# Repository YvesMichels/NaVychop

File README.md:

# navychop

**Autonomous flight experimentation platform — RC aircraft / embedded navigation / AI-assisted development**

`navychop` est un projet **scientifique, technique et ludique** consacré à l'expérimentation autour des pilotes autonomes pour aéronefs.

L'objectif est de construire, avec des moyens essentiellement amateurs, une chaîne complète de navigation et de pilotage autonome : **capteurs → estimation d'état → contrôle → actionneurs → télémétrie**, tout en explorant les limites de ce qui peut être réalisé avec une architecture embarquée légère.

Le projet sert également d'expérimentation sur une autre question :

> **Jusqu'où un projet technique développé par une seule personne, assistée par des IA génératives, peut-il aller face aux méthodes et moyens traditionnellement disponibles dans l'industrie ?**

Il ne s'agit pas de reproduire une architecture avionique industrielle certifiée, mais de mesurer concrètement les capacités, les limites, les compromis et les difficultés rencontrées lorsqu'une approche individuelle s'appuie fortement sur les outils modernes d'IA.

---

## Objectifs

Le projet poursuit plusieurs objectifs complémentaires :

* expérimenter les techniques de **navigation inertielle et de pilotage automatique** ;
* développer une centrale de navigation embarquée autour d'un microcontrôleur ;
* exploiter et fusionner plusieurs capteurs : IMU, baromètre, magnétomètre, GPS et éventuellement vision ;
* développer des lois de commande adaptées à un aéronef léger ;
* expérimenter différentes architectures d'estimation et de contrôle ;
* étudier les contraintes de calcul, de mémoire, de latence et de robustesse d'un système embarqué ;
* développer une chaîne complète allant du matériel embarqué au poste sol ;
* réaliser des essais en conditions réelles sur un aéronef radiocommandé ;
* utiliser les IA génératives comme **assistant de développement et de recherche**, et mesurer concrètement leur apport.

Une attention particulière est portée à la distinction entre :

1. ce qui est **théoriquement possible** ;
2. ce qui est **réalisable avec le matériel disponible** ;
3. ce qui fonctionne réellement **en simulation ou sur banc** ;
4. ce qui fonctionne **en vol**.

---

## Philosophie du projet

`navychop` est volontairement développé comme un projet personnel à vocation expérimentale.

Le but n'est pas de produire immédiatement un système industriel, certifiable ou commercialisable. Le but est au contraire de pouvoir tester rapidement des idées, constater leurs limites et conserver les résultats des expériences.

Le projet cherche notamment à répondre expérimentalement à des questions telles que :

* Quelle complexité de pilote automatique peut être embarquée sur une architecture très contrainte ?
* Quelle précision peut-on obtenir avec des capteurs grand public ?
* Jusqu'où peut-on pousser une architecture développée par une seule personne ?
* Quelles parties d'un système avionique nécessitent réellement une expertise spécialisée ?
* Quelles tâches peuvent être efficacement déléguées à une IA générative ?
* Où l'IA générative atteint-elle ses limites lorsqu'elle doit raisonner sur un système physique réel ?
* Dans quelle mesure une personne assistée par IA peut-elle atteindre une productivité comparable à celle d'une petite équipe technique sur certaines tâches ?

L'IA est donc considérée comme un **outil d'ingénierie**, et non comme une autorité technique.

Les hypothèses proposées par les modèles sont vérifiées autant que possible par le calcul, la simulation, les mesures sur banc et les essais en vol.

---

# Architecture

Le projet est organisé autour de plusieurs éléments :

```text
                    ┌──────────────────────┐
                    │     Poste sol        │
                    │                      │
                    │ Configuration        │
                    │ Commandes            │
                    │ Télémétrie           │
                    │ Enregistrement        │
                    └──────────┬───────────┘
                               │
                             LoRa
                               │
                    ┌──────────▼───────────┐
                    │ Centrale de navigation│
                    │                       │
                    │ ESP32                 │
                    │                       │
                    │ ┌───────────────────┐ │
                    │ │ Estimation d'état │ │
                    │ └───────────────────┘ │
                    │          │            │
                    │ ┌────────▼───────────┐│
                    │ │ Contrôle de vol    ││
                    │ └────────┬───────────┘│
                    │          │            │
                    │      Actionneurs      │
                    │          │            │
                    │      Capteurs         │
                    └───────────────────────┘
```

La centrale de navigation est basée sur un **ESP32** et communique avec différents capteurs et périphériques.

L'architecture est conçue pour pouvoir faire évoluer séparément :

* l'acquisition des capteurs ;
* l'estimation d'attitude et d'état ;
* la navigation ;
* les lois de commande ;
* la communication ;
* l'enregistrement des données ;
* le poste sol.

---

# Matériel

Le système est actuellement validé sur un aéronef radiocommandé expérimental.

L'avion est volontairement réalisé avec des matériaux très simples, principalement des **plaques de polystyrène fines (~2 mm)**.

Ordres de grandeur :

| Paramètre                            |                               Valeur |
| ------------------------------------ | -----------------------------------: |
| Envergure                            |                               ~1,4 m |
| Longueur                             |                                 ~1 m |
| Masse à vide / configuration de base |                                ~1 kg |
| Structure                            |                      Polystyrène fin |
| Motorisation                         |                           Électrique |
| Pilotage                             | Elevons / commandes conventionnelles |
| Centrale de navigation               |                                ESP32 |

Ces caractéristiques ne constituent pas une spécification figée : l'aéronef et son électronique sont susceptibles d'évoluer au cours des expérimentations.

---

# Centrale de navigation

La centrale de navigation constitue une partie importante du projet.

Elle regroupe notamment :

* microcontrôleur **ESP32** ;
* IMU ;
* baromètre ;
* magnétomètre ;
* GPS ;
* liaison radio longue portée 433MHz ;
* interface avec un système de vision ;
* sorties de commande des servomoteurs ;
* enregistrement des données de vol.

Le brochage, les paramètres et les interfaces peuvent évoluer avec les versions matérielles.

Les informations relatives au câblage et aux versions de la carte doivent donc être considérées comme **versionnées avec le matériel correspondant**.

---

# Bibliothèques embarquées

Les bibliothèques présentes dans ce dépôt sont principalement des composants **spécifiques à la centrale de navigation développée dans le cadre de `navychop`**.

Elles ne doivent donc pas nécessairement être considérées comme des bibliothèques génériques ou autonomes.

Elles peuvent dépendre :

* du brochage de la carte ;
* des périphériques effectivement présents ;
* de la structure des données du projet ;
* du protocole de communication interne ;
* du format des données de télémétrie ;
* des contraintes de calcul et de mémoire de l'ESP32.

Lorsqu'une bibliothèque tierce est utilisée, elle doit autant que possible être clairement identifiée comme telle, avec sa version et sa licence.

Les bibliothèques développées spécifiquement pour `navychop` sont distinguées des dépendances externes afin de faciliter leur réutilisation.

---

# Développement assisté par IA

Une caractéristique importante du projet est l'utilisation intensive d'**IA génératives comme assistants de développement**.

Elles peuvent notamment être utilisées pour :

* proposer des architectures logicielles ;
* générer ou modifier du code ;
* expliquer des algorithmes ;
* rechercher des erreurs ;
* analyser des résultats expérimentaux ;
* produire de la documentation ;
* challenger certaines hypothèses techniques ;
* générer des outils de test.

Cependant, le code généré par une IA n'est pas considéré comme automatiquement correct.

Pour les fonctions ayant un impact sur le comportement de l'aéronef, les propositions sont confrontées autant que possible à :

* la documentation des composants ;
* les équations et modèles physiques ;
* des tests unitaires ;
* des simulations ;
* des essais sur banc ;
* des mesures instrumentées ;
* des essais en vol progressifs.

Le projet constitue ainsi également une expérimentation sur le **développement logiciel humain + IA dans un système cyber-physique réel**.

---

# Expérimentation et validation

Le développement suit autant que possible une progression :

```text
Théorie
   ↓
Simulation / calcul
   ↓
Test logiciel
   ↓
Test sur banc
   ↓
Test moteur arrêté
   ↓
Essai en conditions contrôlées
   ↓
Essai en vol
   ↓
Analyse des données
   ↓
Modification
```

Les résultats d'un essai réel peuvent donc conduire à remettre en question une hypothèse précédemment considérée comme correcte.

Une fonctionnalité présente dans le code ne doit pas être considérée comme **validée en vol** tant qu'un essai approprié ne l'a pas démontré.

---

# Données de vol

Les données enregistrées pendant les expérimentations sont utilisées pour :

* analyser le comportement de l'aéronef ;
* caractériser les capteurs ;
* analyser les boucles de contrôle ;
* identifier les instabilités ;
* comparer différentes configurations ;
* reproduire certains problèmes ;
* mesurer les performances du système.

Lorsque cela est pertinent, les expérimentations peuvent être accompagnées de leur configuration matérielle et logicielle afin de permettre leur reproduction.

---

# État du projet

Le projet est **expérimental et en développement actif**.

Les interfaces, protocoles, paramètres, algorithmes et structures de données peuvent changer sans garantie de compatibilité avec les versions précédentes.

Les fonctionnalités peuvent avoir différents niveaux de maturité :

* **Prototype** — implémentation initiale, non validée ;
* **Bench tested** — testé sur banc ;
* **Flight tested** — testé en vol ;
* **Experimental** — fonction opérationnelle mais encore en cours d'étude.

Une fonctionnalité fonctionnant sur l'aéronef ne doit pas pour autant être considérée comme adaptée à une utilisation critique ou à un autre aéronef sans nouvelle validation.

---

# Sécurité

`navychop` est un projet expérimental concernant un aéronef radiocommandé.

**Le logiciel et le matériel fournis dans ce dépôt ne sont pas des systèmes avioniques certifiés.**

Toute utilisation sur un aéronef doit être précédée de validations adaptées au matériel, à l'environnement et au niveau de risque considéré.

Les essais doivent notamment prendre en compte :

* la perte de liaison radio ;
* les erreurs de capteurs ;
* les erreurs d'estimation ;
* les saturations des commandes ;
* les défauts logiciels ;
* les pertes d'alimentation ;
* les comportements inattendus du pilote automatique ;
* la possibilité de reprendre le contrôle manuellement.

Le système doit toujours disposer d'un moyen approprié de récupération ou d'interruption du contrôle automatique lors des essais.

**Ne pas utiliser ce projet comme base directe pour le contrôle d'un aéronef habité ou d'un système dont la défaillance pourrait mettre des personnes en danger.**

**Tout vol doit être effectué dans des conditions autorisée par la loi en vigueur.**

---

# Reproductibilité

L'objectif est de documenter suffisamment le projet pour qu'une autre personne puisse reproduire une partie significative des expérimentations.

Lorsque cela est pertinent, les commits, versions matérielles, paramètres et résultats d'essais doivent être associés aux expérimentations correspondantes.

Les changements susceptibles de modifier le comportement en vol doivent idéalement être identifiables dans l'historique Git.

---

# Git et GitLab

Le dépôt utilise Git afin de conserver l'historique du développement et GitLab pour l'hébergement du projet.

Les contributions doivent autant que possible :

* utiliser des commits atomiques ;
* employer des messages de commit explicites ;
* éviter de mélanger refactoring, nouvelle fonctionnalité et correction expérimentale dans un même commit ;
* documenter les changements ayant un impact sur le comportement de l'aéronef ;
* conserver les configurations nécessaires à la reproduction d'une expérience ;
* utiliser les **Issues** pour les bugs, idées et problèmes identifiés ;
* utiliser les **Merge Requests** lorsque plusieurs branches ou contributeurs sont impliqués ;
* utiliser les **Tags/Releases** pour identifier les versions importantes du logiciel ou du matériel.

Pour les modifications importantes, une Issue peut servir à documenter :

```text
Problème
↓
Hypothèse
↓
Modification
↓
Test
↓
Résultat
↓
Conclusion
```

Cette approche permet de conserver une trace expérimentale plutôt qu'un simple historique de code.

---

# Dépendances

Les dépendances externes doivent être identifiées explicitement lorsqu'elles sont nécessaires à la compilation ou au fonctionnement du projet.

Pour chaque dépendance importante, il est recommandé de conserver :

* nom ;
* version ;
* source officielle ;
* licence ;
* raison de son utilisation.

Les bibliothèques développées spécifiquement pour `navychop` sont séparées conceptuellement des dépendances tierces.

---

# Licence

| Contenu | Licence |
|---|---|
| Code (`nav/`, `vision/`, `peripherals/`, `common/`, `python/`, `matlab/`) | MIT (`LICENSE.md`) |
| Matériel (`electronics/`, `mechanical/`) | CERN-OHL-P v2 (`LICENSE-HARDWARE.md`) |
| Documentation (`documentation/`) | CC BY 4.0 (`LICENSE-DOCS.md`) |

Voir aussi [DISCLAIMER.md](DISCLAIMER.md) : avertissement sur la sécurité et la réglementation.

---

# Contribution

Les contributions, corrections et discussions techniques sont les bienvenues.

Avant de proposer une modification importante, il est recommandé d'ouvrir une Issue afin de discuter de l'approche envisagée.

Les contributions doivent privilégier :

* la reproductibilité ;
* la simplicité ;
* la documentation ;
* les tests ;
* l'explicitation des hypothèses ;
* la séparation entre fonctionnalités expérimentales et fonctionnalités validées.

---

# Pourquoi « navychop » ?

`navychop` est le nom du projet et de son environnement logiciel. Ce nom provien de l'association du pseudo Vychop et 'nav' pour navigation. 

Le nom n'a pas vocation à constituer une marque commerciale ou une désignation aéronautique officielle.

---

## Avertissement

Ce dépôt documente une expérimentation personnelle.

Les résultats présentés sont dépendants du matériel, du logiciel, de la configuration de l'aéronef et des conditions expérimentales.

**Un résultat obtenu dans le cadre de `navychop` ne constitue pas une garantie de comportement dans une autre configuration.**

---

## Auteur

Projet développé individuellement par Vychop (Yves MICHELS) avec l'assistance d'outils d'IA générative.

Le projet cherche notamment à documenter ce qu'une personne seule peut réaliser en combinant :

* connaissances scientifiques et techniques ;
* prototypage électronique ;
* développement logiciel ;
* expérimentation physique ;
* outils open source ;
* IA génératives.

L'objectif n'est pas de démontrer que l'IA remplace l'ingénierie, mais de **mesurer expérimentalement ce qu'elle permet de réaliser lorsqu'elle est utilisée comme outil par un ingénieur.**

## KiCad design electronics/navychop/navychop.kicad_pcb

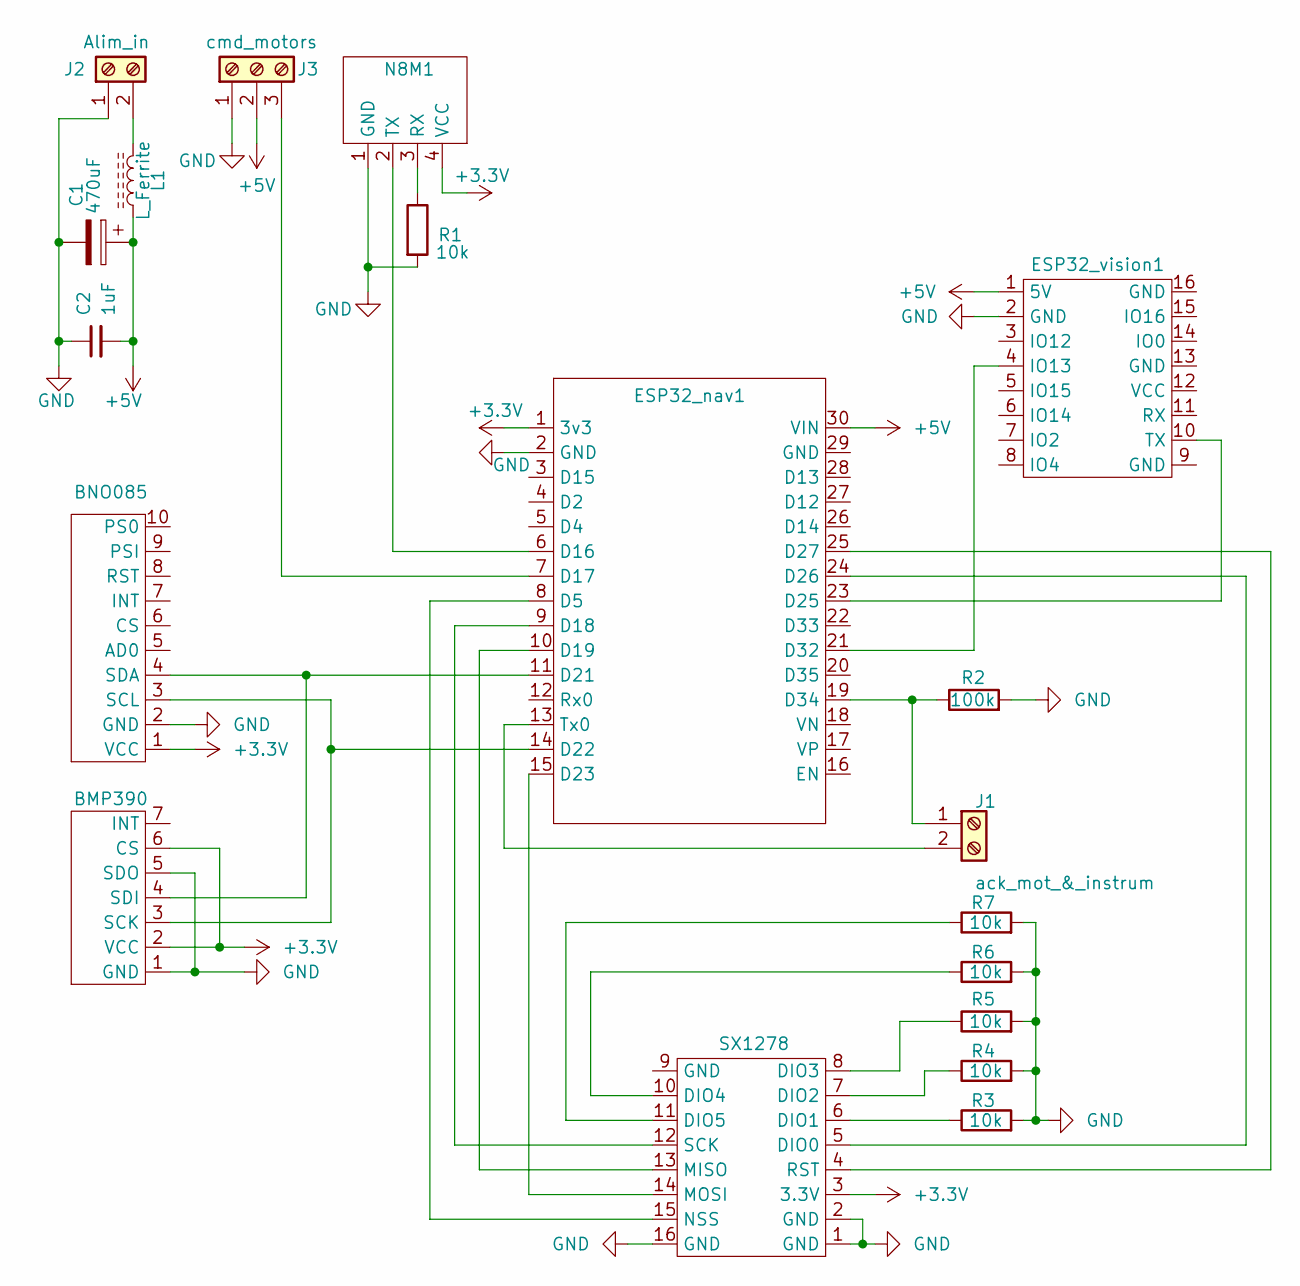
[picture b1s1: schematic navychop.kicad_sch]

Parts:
BMP390: BMP390
BNO085: BNO085
C1: 470uF; CP_Radial_D5.0mm_P2.50mm
C2: 1uF; C_Disc_D5.0mm_W2.5mm_P2.50mm
ESP32_nav1: ESP32_board_30pins
ESP32_vision1: ESP32_CAM
J1: ack_mot_&_instrum; TerminalBlock_Phoenix_MKDS-1,5-2-5.08_1x02_P5.08mm_Horizont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
J2: Alim_in; TerminalBlock_Phoenix_MKDS-1,5-2-5.08_1x02_P5.08mm_Horizont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
J3: cmd_motors; TerminalBlock_Phoenix_MKDS-3-3-5.08_1x03_P5.08mm_Horizontal
L1: L_Ferrite; L_Radial_D6.0mm_P4.00mm
N8M1: NEO_N8M
R1, R3, R4, R5, R6, R7: 10k; R_Axial_DIN0204_L3.6mm_D1.6mm_P7.62mm_Horizontal
R2: 100k; R_Axial_DIN0204_L3.6mm_D1.6mm_P7.62mm_Horizontal
SX1278: LoRa_SX1278

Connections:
+3.3V: BMP390.2 (VCC), BMP390.6 (CS), BNO085.1 (VCC), ESP32_nav1.1 (3v3), N8M1.4 (VCC), SX1278.3 (3.3V)
+5V: C1.1, C2.2, ESP32_nav1.30 (VIN), ESP32_vision1.1 (5V), J3.2, L1.1
GND: BMP390.1 (GND), BMP390.5 (SDO), BNO085.2 (GND), C1.2, C2.1, ESP32_nav1.2 (GND), ESP32_vision1.2 (GND), J2.1, J3.1, N8M1.1 (GND), R1.2, R2.2, R3.2, R4.2, R5.2, R6.2, R7.2, SX1278.1 (GND), SX1278.2 (GND), SX1278.16 (GND)
unnamed: BMP390.3 (SCK), BNO085.3 (SCL), ESP32_nav1.14 (D22)
unnamed: BMP390.4 (SDI), BNO085.4 (SDA), ESP32_nav1.11 (D21)
unnamed: ESP32_nav1.8 (D5), SX1278.15 (NSS)
unnamed: ESP32_nav1.6 (D16), N8M1.2 (TX)
unnamed: ESP32_nav1.7 (D17), J3.3
unnamed: ESP32_nav1.9 (D18), SX1278.12 (SCK)
unnamed: ESP32_nav1.10 (D19), SX1278.13 (MISO)
unnamed: ESP32_nav1.15 (D23), SX1278.14 (MOSI)
unnamed: ESP32_nav1.23 (D25), ESP32_vision1.10 (TX)
unnamed: ESP32_nav1.24 (D26), SX1278.5 (DIO0)
unnamed: ESP32_nav1.25 (D27), SX1278.4 (RST)
unnamed: ESP32_nav1.21 (D32), ESP32_vision1.4 (IO13)
unnamed: ESP32_nav1.19 (D34), J1.1, R2.1
unnamed: ESP32_nav1.13 (Tx0), J1.2
unnamed: J2.2, L1.2
unnamed: N8M1.3 (RX), R1.1
unnamed: R3.1, SX1278.6 (DIO1)
unnamed: R4.1, SX1278.7 (DIO2)
unnamed: R5.1, SX1278.8 (DIO3)
unnamed: R6.1, SX1278.10 (DIO4)
unnamed: R7.1, SX1278.11 (DIO5)

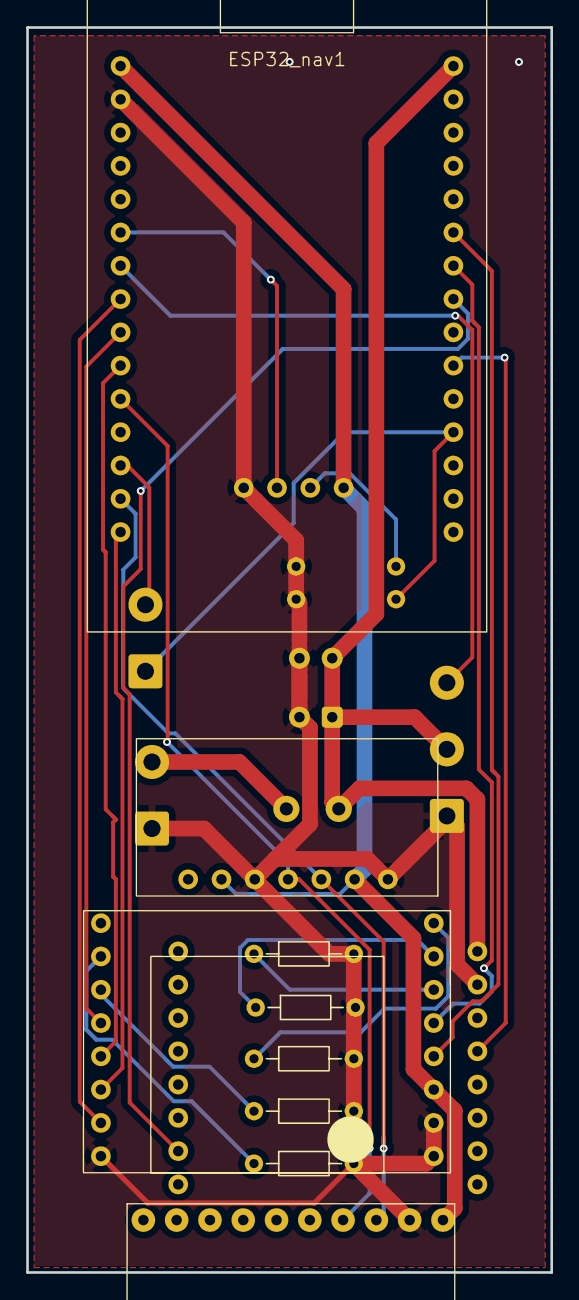
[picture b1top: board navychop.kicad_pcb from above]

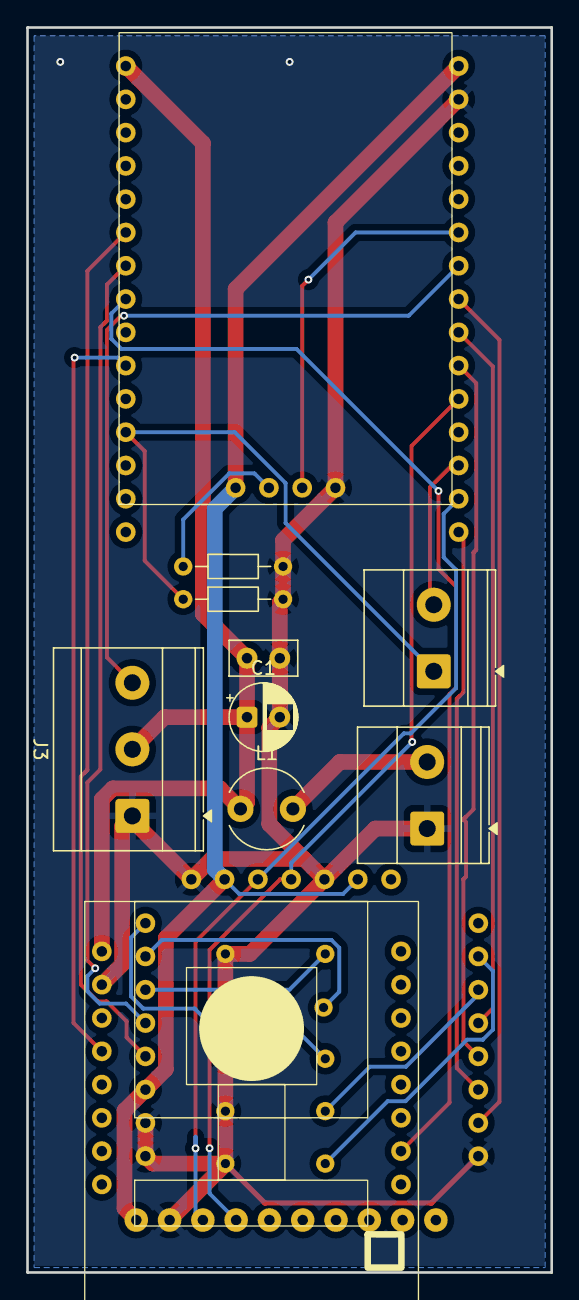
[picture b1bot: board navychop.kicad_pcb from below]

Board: 2 copper layers, 40.0 x 95.0 mm, 19 parts (10 on the bottom side), 24 nets.

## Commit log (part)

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2025-12-22 initialisation de la navigation (esp8266)
2025-12-22 initialisation de la vision (esp32-CAM)
2025-12-22 ajout de fonctions de transformation dans vision
2026-01-01 transformation fonctionnelle + code de vérification unitaire du sinus en virgule fixe et des transformations (translations, zoom, rotation)
2026-01-04 optimisation transformation + calcul gradient virgule fixe (non fonctonnel) + transmission debogue (dans image_process)
2026-01-11 ajout du calcul d'image décimée en embarqué + test estimation de mouvement en python
2026-01-24 pré estimation du mouvement sur ESP32 + vérification python
2026-01-27 estimation de mouvement 2 échelles avec init hexhaustive + mesure du temps
2026-01-29 optimisation timming 150ms / image
2026-04-26 carte electronique et mesures pour asservissement sans angles
2026-05-08 ajout de la communication LoRa à la navigation (en cours de test)
2026-05-10 asservissement testé sur avion au sol (a vérifier : limites sur la gouverne 'yaw')
2026-05-23 navigation : estimation de l'altitude relative + initialisation du cap par défaut + réorganisation architecture (gestion des responsabilité des paramètres par défaut)
2026-05-30 simplification asservissement pour la prise en main en vol (uniquement en pitch et roll)
2026-05-30 ajout de la bibliotheque datalink : les paramètres de controle peuvent être mis à jour en direct via liaison LoRa Passage en SF 9 pour plus de robustesse de la liaison LoRa (toujours compatible commu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
2026-06-09 sauvegarde des logs en flash commandé par LoRa + lecture UART après redémarrage fonctionnel
2026-06-13 ajout d'un outil de paramétrage live avec pilotage intégré.
2026-06-14 ajout d'une fonction d'auto-génération de la bibliothèque "datalink" basée sur le fichier commun de parameters.json
